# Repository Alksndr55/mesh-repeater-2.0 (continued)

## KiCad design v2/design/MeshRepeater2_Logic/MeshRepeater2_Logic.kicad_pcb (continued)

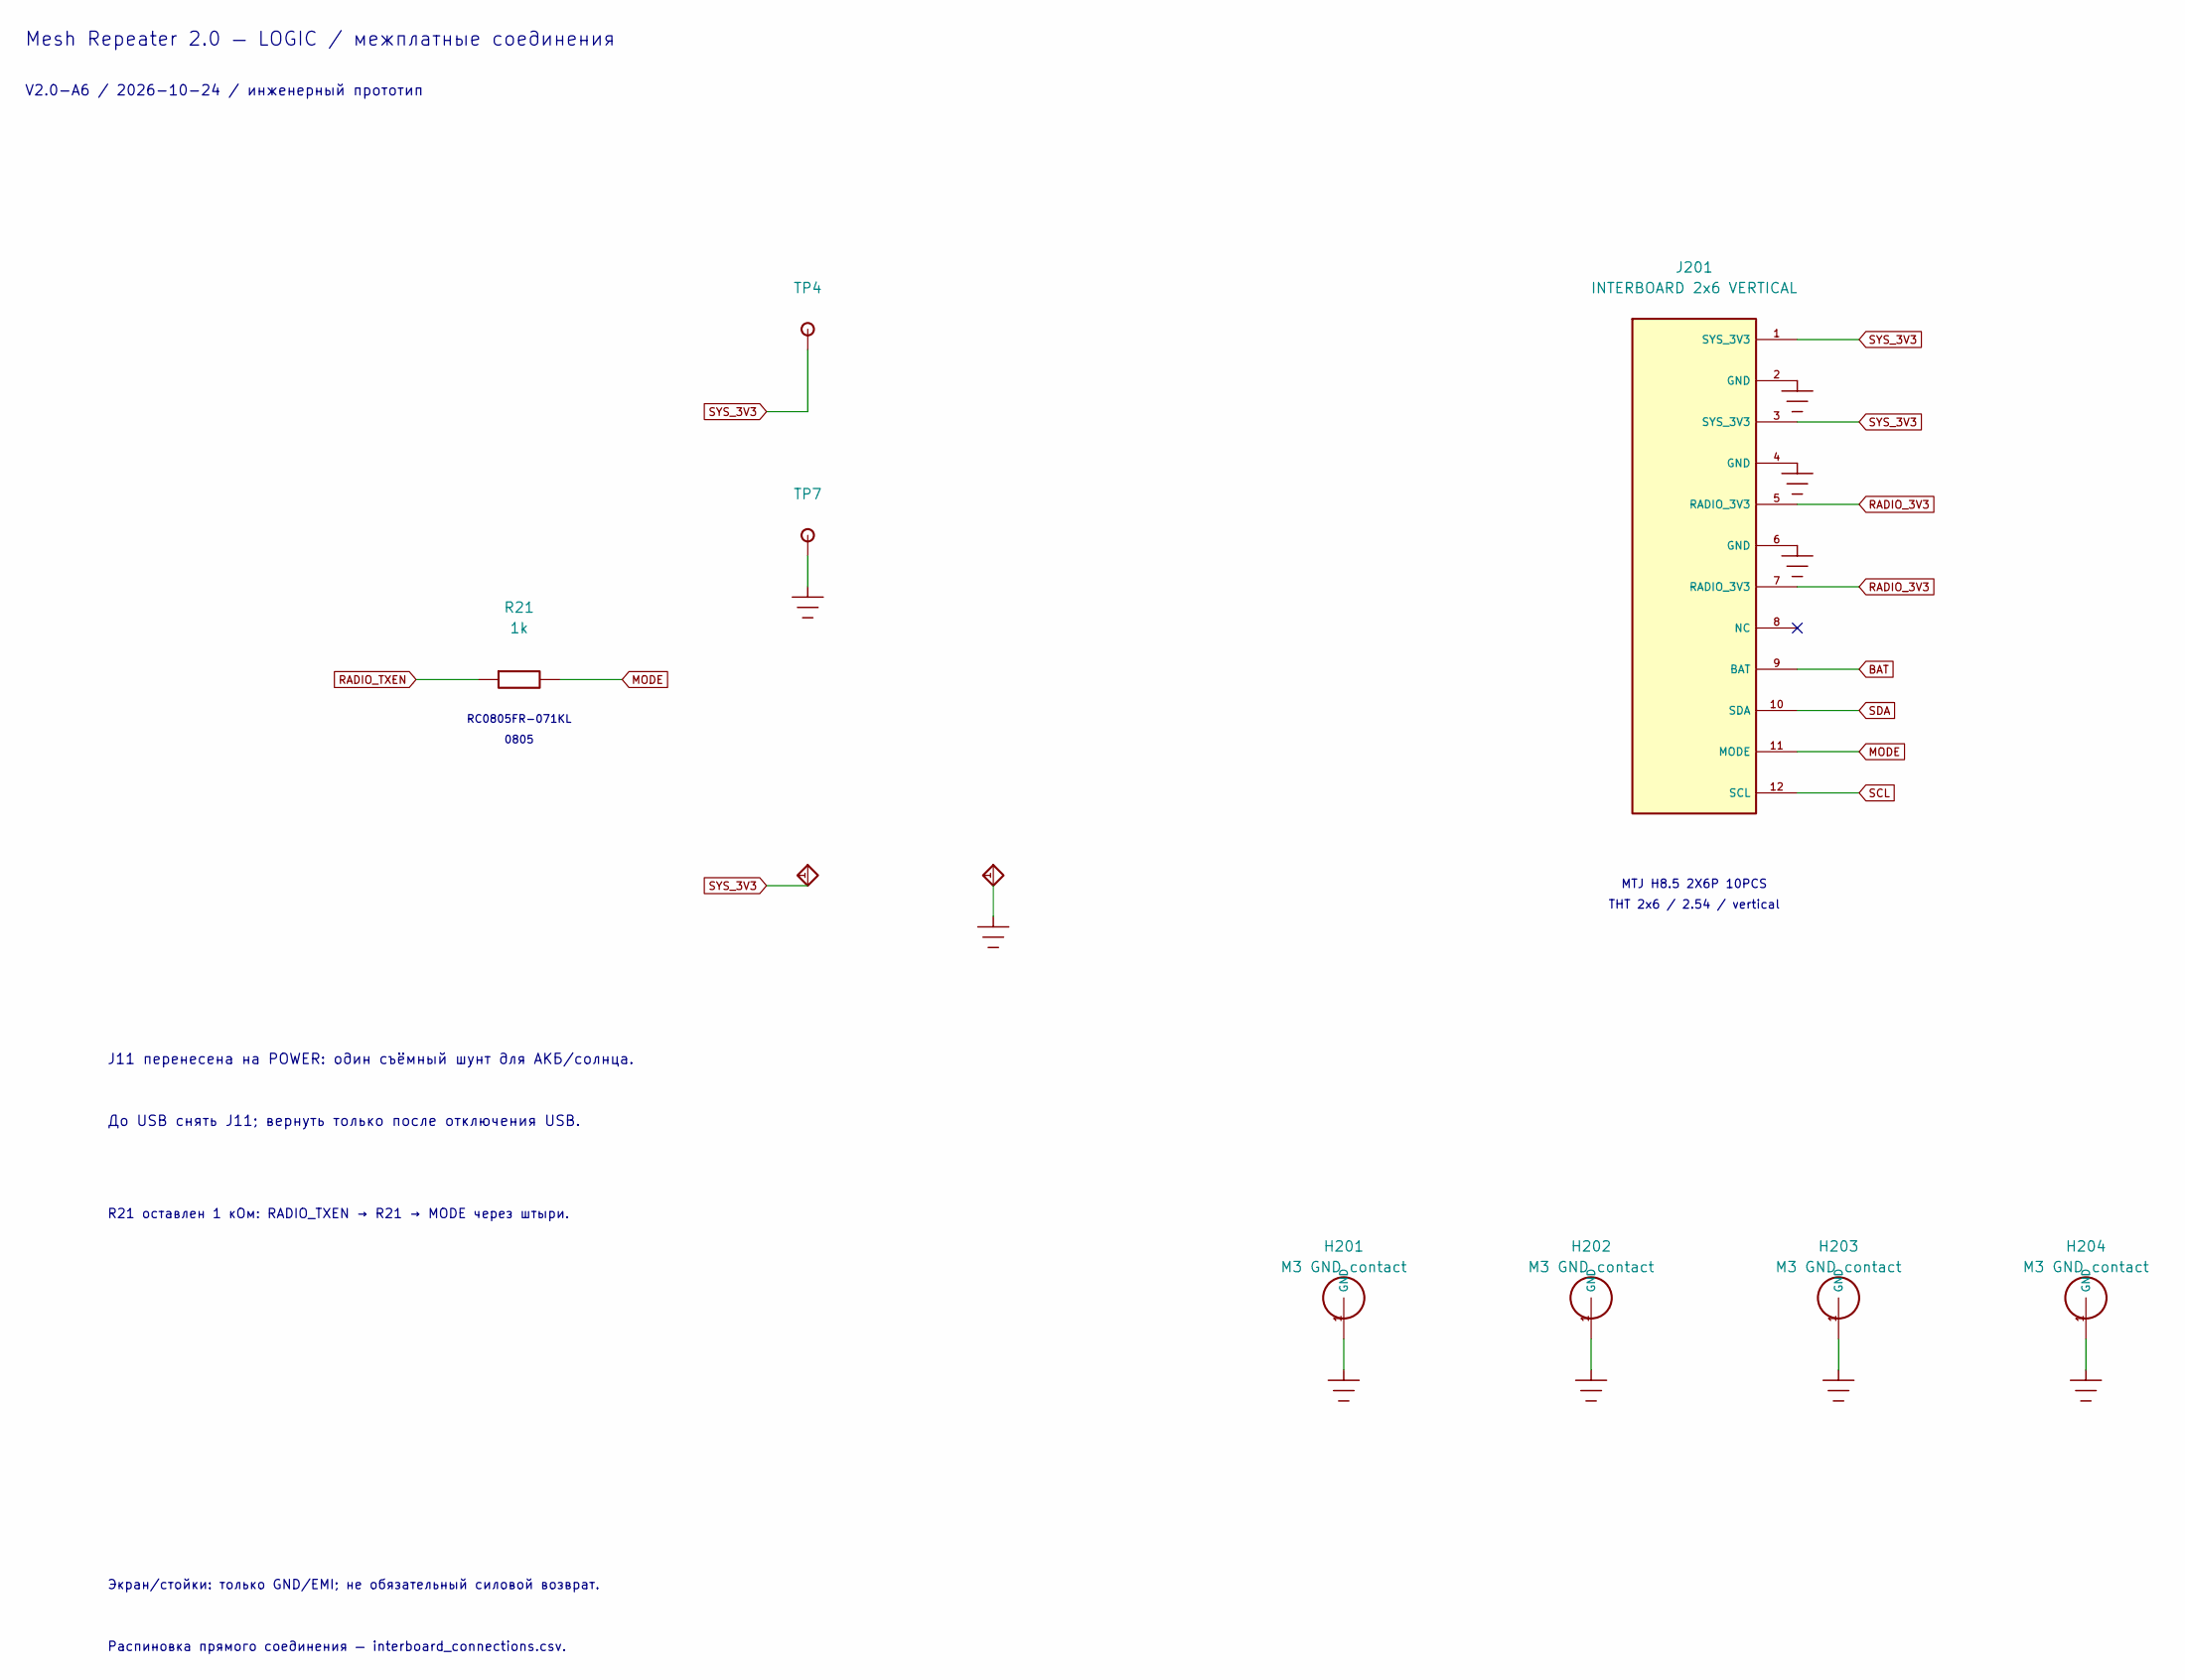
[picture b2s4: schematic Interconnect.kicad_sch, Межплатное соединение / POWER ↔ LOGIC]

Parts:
H201: M3 GND contact; GND_M3_D3.2_OD6__V2_H201; MPN PCB land M3 GND OD6 drill3.2
H202: M3 GND contact; GND_M3_D3.2_OD6__V2_H202; MPN PCB land M3 GND OD6 drill3.2
H203: M3 GND contact; GND_M3_D3.2_OD6__V2_H203; MPN PCB land M3 GND OD6 drill3.2
H204: M3 GND contact; GND_M3_D3.2_OD6__V2_H204; MPN PCB land M3 GND OD6 drill3.2
J201: INTERBOARD 2x6 VERTICAL; Ali_PinSocket_2x06_P2.54_H8.5_v2_mirror__V2_J201; MPN MTJ H8.5 2X6P 10PCS
R21: 1k; R_0805_2012Metric__V2_R21; MPN RC0805FR-071KL
TP4: SYS_3V3; TestPoint_Pad_D1.5mm__V2_TP4
TP7: GND; TestPoint_Pad_D1.5mm__V2_TP7

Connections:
BAT: J201.9 (BAT); also elsewhere on the board
GND: H201.1, H202.1, H203.1, H204.1, J201.2 (GND), J201.4 (GND), J201.6 (GND), TP7.1; also elsewhere on the board
MODE: J201.11 (MODE), R21.2
RADIO_3V3: J201.5 (RADIO_3V3), J201.7 (RADIO_3V3); also elsewhere on the board
RADIO_TXEN: R21.1; also elsewhere on the board
SCL: J201.12 (SCL); also elsewhere on the board
SDA: J201.10 (SDA); also elsewhere on the board
SYS_3V3: J201.1 (SYS_3V3), J201.3 (SYS_3V3), TP4.1; also elsewhere on the board

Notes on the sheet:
0805
THT 2x6 / 2.54 / vertical
V2.0-A6 / 2026-10-24 / инженерный прототип
R21 оставлен 1 кОм: RADIO_TXEN → R21 → MODE через штыри.
Экран/стойки: только GND/EMI; не обязательный силовой возврат.
J11 перенесена на POWER: один съёмный шунт для АКБ/солнца.
Mesh Repeater 2.0 — LOGIC / межплатные соединения
До USB снять J11; вернуть только после отключения USB.
RC0805FR-071KL
Распиновка прямого соединения — interboard_connections.csv.
MTJ H8.5 2X6P 10PCS

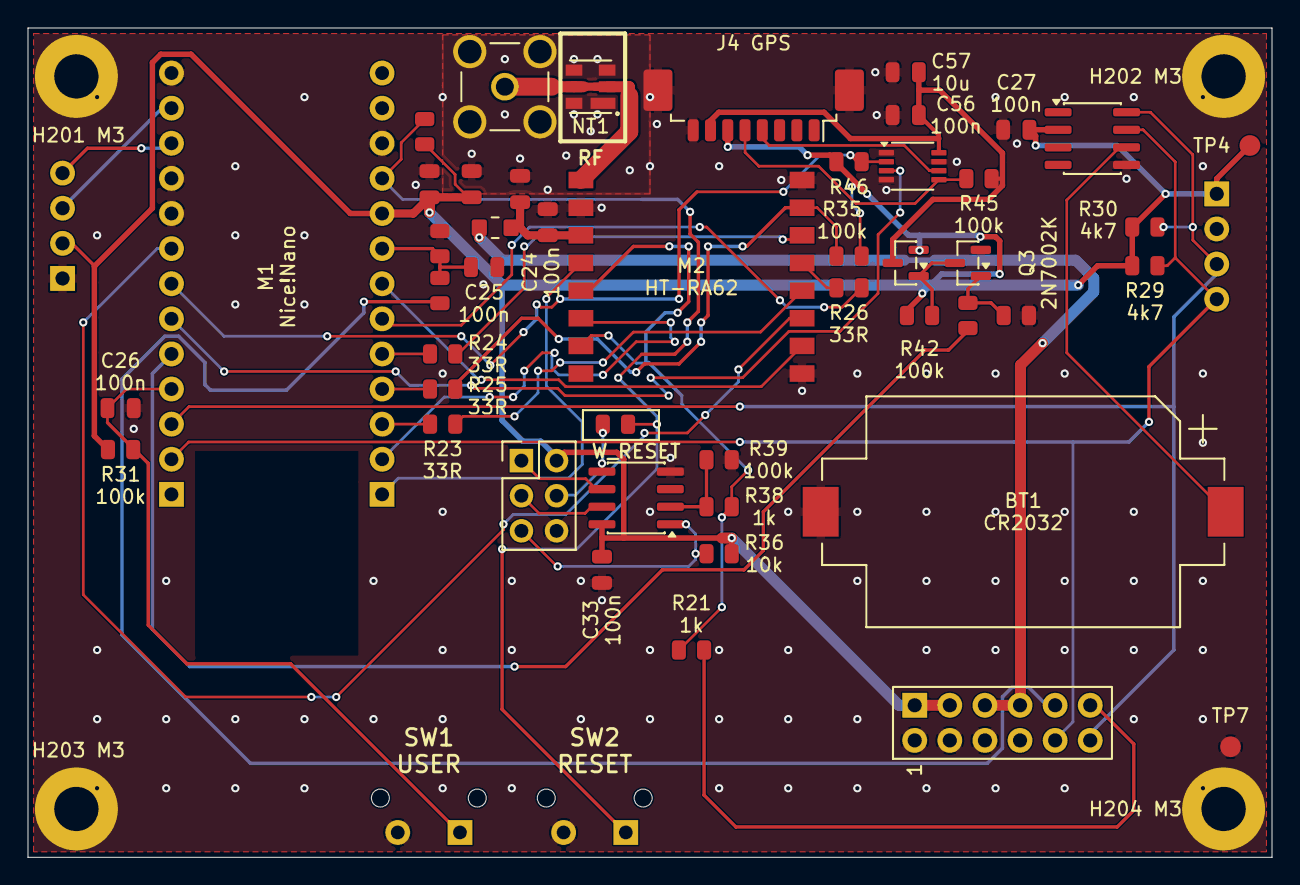
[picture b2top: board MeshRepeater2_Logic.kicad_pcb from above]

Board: 2 copper layers, 90.0 x 60.0 mm, 56 parts (0 on the bottom side), 42 nets.

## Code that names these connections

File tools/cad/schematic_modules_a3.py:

"""Compact module interconnect, controls and battery measurement."""
from schematic_core import Sheet

def build():
    s=Sheet('Modules','Nice!Nano, HT-RA62, управление и измерение батареи',3)
    s.sym('M1',88.9,80.01).sym('M2',215.9,80.01)
    for a,b in [(1,4),(2,6),(7,10),(21,11)]:s.wire(('M1',a),('M2',b))
    for ref,a,b,x in [('R23',3,12,153.67),('R24',5,14,153.67),('R25',4,15,153.67),('R26',6,13,175.26)]:
        y=s.pin('M1',a)[1]
        s.sym(ref,x,y,'R_H_REV' if ref=='R26' else 'R_H',label=(x-3.81,y-1.905,x+5.08,y-1.905))
        if ref=='R26':s.wire(('M1',a),(ref,2));s.wire((ref,1),('M2',b))
        else:s.wire(('M1',a),(ref,1));s.wire((ref,2),('M2',b))
    for a,n in [(1,'RADIO_RST'),(2,'RADIO_DIO1'),(7,'RADIO_BUSY'),(21,'RADIO_RXEN')]:s.label(n,(142.24,s.pin('M1',a)[1]))
    for pin in [12,13]:s.nc('M1',pin)
    from schematic_core import MODEL
    for pin in ([8] if MODEL.get('rf_connector') else [1,8]):s.nc('M2',pin)
    if MODEL.get('rf_connector'):
        rf_y=116.84 if MODEL.get('rf_filter_option') else 101.6
        s.sym('J13',317.5,rf_y,'COAX')
        ant=s.pin('M2',1)
        if MODEL.get('rf_filter_option'):
            s.sym('FL1',279.4,rf_y,'SAW')
            s.sym('NT1',279.4,104.14,'NETTIE')
            s.wire(ant,(246.38,ant[1]),(246.38,rf_y),('FL1',2))
            s.wire(('FL1',5),('J13',1))
            s.wire(('NT1',1),(259.08,104.14),(259.08,rf_y));s.dot((259.08,rf_y))
            s.wire(('NT1',2),(299.72,104.14),(299.72,rf_y));s.dot((299.72,rf_y))
            s.wire((254.0,rf_y),(254.0,119.38),(248.92,119.38));s.dot((254.0,rf_y))
            s.label('ANT_RF',(248.92,119.38),angle=180)
            s.wire((304.8,rf_y),(304.8,121.92),(299.72,121.92));s.dot((304.8,rf_y))
            s.label('ANT_SMA',(299.72,121.92),angle=180)
            for pin in (1,3,4,6):s.wire(('FL1',pin),(s.pin('FL1',pin)[0],132.08))
            s.wire((271.78,132.08),(287.02,132.08))
            s.dot((276.86,132.08));s.dot((281.94,132.08));s.ground((287.02,132.08),2.54)
            s.text('FL1 — опция 868–870 МГц, TX ≤ +13 dBm.\nДо установки разрезать медь NT1 под FL1.\nБез FL1 оставить NT1 целой.',266.7,151.13,1.05,'left')
        else:
            s.wire(ant,(246.38,ant[1]),(246.38,rf_y),('J13',1))
            s.label('ANT_RF',(269.24,rf_y))
        s.ground(('J13',2),2.54)
    for pin in [8,10,17,18,19,20,24,25,15,16]:s.net('M1',pin,5.08)
    s.nc('M1',14)
    # TXEN is DIO2: only a high-impedance sense is taken.
    tx=s.pin('M2',5);dio=s.pin('M2',7);x=182.88
    s.wire(tx,(x,tx[1]),(x,dio[1]),dio)
    s.wire((x,dio[1]),(x,114.3));s.dot((x,dio[1]))
    s.global_stub('RADIO_TXEN',(x,114.3),(187.96,114.3),angle=180)
    s.sym('R35',162.56,121.92,'R_H');s.net('R35',1,5.08)
    cs_y=s.pin('M2',15)[1]
    s.wire(('R35',2),(177.8,121.92),(177.8,cs_y));s.dot((177.8,cs_y))
    for ref,pins in [('M1',[11,22,23,26]),('M2',[2,9,16])]:
        coords=[s.pin(ref,n) for n in pins];y=max(p[1] for p in coords)+3.81
        for x,a in coords:s.wire((x,a),(x,y))
        s.wire((coords[0][0],y),(coords[-1][0],y))
        for x,a in coords[1:-1]:s.dot((x,y))
        s.ground((coords[1][0],y),2.54)
    # User-requested direct feed to the module3V3 pin.
    y=s.pin('M1',9)[1]
    s.wire(('M1',9),(30.48,y),(30.48,39.37))
    s.global_stub('SYS_3V3',(30.48,39.37),(25.4,39.37))
    s.sym('C23',251.46,73.66,'C_V').sym('C24',274.32,73.66,'C_V')
    y=s.pin('M2',3)[1]
    s.wire(('M2',3),(284.48,y));s.label('RADIO_LOCAL_3V3',(274.32,y))
    s.sym('FB1',251.46,38.1,'L_H')
    s.global_stub('RADIO_3V3',('FB1',1),(238.76,38.1))
    s.wire(('FB1',2),(284.48,38.1),(284.48,y))
    for ref in ['C23','C24']:
        x,_=s.pin(ref,1);s.wire((x,y),(ref,1));s.dot((x,y));s.ground((ref,2),2.54)
    s.sym('C21',218.44,167.64,'C_V').sym('C22',243.84,167.64,'C_V')
    s.wire((218.44,157.48),(243.84,157.48));s.global_stub('SYS_3V3',(218.44,157.48),(210.82,157.48))
    for ref in ['C21','C22']:
        x,_=s.pin(ref,1);s.wire((x,157.48),(ref,1));s.ground((ref,2),2.54)
    s.sym('R27',30.48,119.38,'R_V').sym('R28',30.48,139.7,'R_V').sym('C25',55.88,139.7,'C_V')
    s.net('R27',1,5.08)
    s.wire(('R27',2),(30.48,129.54),('R28',1));s.dot((30.48,129.54))
    s.wire((30.48,129.54),(55.88,129.54),('C25',1));s.global_stub('BAT_ADC',(55.88,129.54),(63.5,129.54),angle=180)
    s.ground(('R28',2),2.54);s.ground(('C25',2),2.54)
    s.sym('SW2',38.1,177.8,'SW_H').sym('SW1',91.44,177.8,'SW_H')
    for ref in ['SW2','SW1']:s.net(ref,1,5.08);s.ground((ref,2),2.54)
    s.sym('R31',104.14,149.86,'R_V').sym('C26',130.81,172.72,'C_V')
    s.net('R31',1,5.08)
    s.wire(('R31',2),(104.14,160.02),(130.81,160.02),('C26',1))
    s.global_stub('USER_BTN',(130.81,160.02),(140.97,160.02),angle=180);s.ground(('C26',2),2.54)
    adc_note=('ADC: BAT/2; τ ≈ 110 мс. Калибровка ADC.'
              if MODEL.get('battery_dividers') else 'ADC: BAT/2; установление ≈ 50 мс.')
    s.text(adc_note,15.24,157.48,1.27)
    s.text('SPI: 33 Ом у драйверов.\n'+('ANT: J13 / SMA, 50 Ом.\n' if MODEL.get('rf_connector') else 'ANT: штатный IPEX.\n')+'TXEN → MODE и watchdog.\nP1.06 свободен.\nBUSY=P0.29; GPS_EN=P0.24.\nGPS_EN=HIGH: питание GPS включено.',228.6,124.46,1.05)
    if MODEL.get('rf_connector'):
        s.text(MODEL['rf_connector']['module_configuration_ru'],317.5,152.4 if MODEL.get('rf_filter_option') else 137.16,1.05,'left')
    s.text('3V3 через J11 на POWER; RAW/BAT: NC. USB-зарядник отключить.\nСнять шунт J11 ДО подключения USB.\nВернуть J11 только после отключения USB.',142.24,188,1.27)
    s.text('POWER: J11 → NT2-звезда → две ветви. Модем: RADIO_3V3 → FB1 → RADIO_LOCAL_3V3.',142.24,210.82,1.15)
    s.text('FB1: DCR ≤20 мОм; около 3 мВ при 150 мА. Проверить броски питания при TX осциллографом.',142.24,218.44,1.15)
    return s

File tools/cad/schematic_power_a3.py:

"""Compact, explicitly wired power sheet for the editable S3 schematic.

Symbols retain their normal size. Coordinates use the 1.27 mm pin grid;
all visible reference/value properties retain the same upright two-line order.
"""
from schematic_core import Sheet,MODEL,PARTS


def _g(x, y):
    return round(x * 1.27, 5), round(y * 1.27, 5)


def _side_label(x, y):
    xx, yy = _g(x, y)
    return xx + 3.81, yy - 1.27, xx + 3.81, yy + 1.27


def _sym(sheet, ref, x, y, style=None, label=None):
    sheet.sym(ref, *_g(x, y), style=style, label=label)


def _ground(sheet, point):
    sheet.ground(point, length=2.54)


def _converter():
    s = Sheet('Converter', 'TPS63802 — питание и двухкаскадный LC-фильтр', 2)
    _sym(s, 'U2', 69, 66,
         label=(*_g(69, 44), *_g(69, 46)))
    _sym(s, 'L2', 69, 31, 'L_H')
    _sym(s, 'C12', 22, 60, 'C_V', _side_label(22, 60))
    _sym(s, 'C13', 39, 60, 'C_V', _side_label(39, 60))
    _sym(s, 'R15', 16, 76, 'R_V', _side_label(16, 76))
    _sym(s, 'R16', 16, 90, 'R_V', _side_label(16, 90))
    _sym(s, 'R17', 31, 90, 'R_V', _side_label(31, 90))
    _sym(s, 'C14', 94, 64, 'C_V', _side_label(94, 64))
    _sym(s, 'R13', 107, 64, 'R_V', _side_label(107, 64))
    _sym(s, 'R14', 107, 82, 'R_V', _side_label(107, 82))
    if 'R18' in PARTS:_sym(s, 'R18', 129, 82, 'R_V', _side_label(129, 82))
    _sym(s, 'TP3', 118, 52)
    if 'TP5' in PARTS:_sym(s, 'TP5', 140, 90)
    if 'TP7' in PARTS:_sym(s, 'TP7', 80, 87)

    # S4.5 reserve sites are wired directly to the same local input/output
    # rails as C12/C14. DNP denotes an empty site, not a chosen capacitance.
    for ref,x in [('C52',22),('C53',39),('C54',94),('C55',112)]:
        _sym(s,ref,x,34,'C_V',_side_label(x,34))
        _ground(s,(ref,2))
    s.wire(_g(16,52),_g(16,26),_g(39,26))
    for ref,x in [('C52',22),('C53',39)]:
        s.wire((ref,1),_g(x,26));s.dot(_g(x,26))
    s.wire(_g(94,26),_g(120,26),_g(120,56));s.dot(_g(120,56))
    for ref,x in [('C54',94),('C55',112)]:
        s.wire((ref,1),_g(x,26));s.dot(_g(x,26))

    # Both local input capacitors are normal vertical shunts below BAT.
    s.wire(_g(16, 52), _g(50, 52), _g(50, 56), ('U2', 10))
    s.global_stub('BAT_SYS' if MODEL.get('battery_monitor') else 'BAT',_g(39,26),_g(47,26),angle=180)
    for ref, x in [('C12', 22), ('C13', 39)]:
        s.wire((ref, 1), _g(x, 52)); s.dot(_g(x, 52))
        _ground(s, (ref, 2))

    # EN divider: BAT -> R15 -> EN_UV -> R16 -> GND.
    if MODEL.get('battery_monitor'):
        s.net('R15',1,7.62)
    else:
        s.wire(('R15', 1), _g(16, 52)); s.dot(_g(16, 52))
    s.wire(('R15', 2), _g(16, 82), ('R16', 1))
    s.wire(('U2', 1), _g(47, 66), _g(47, 82), _g(16, 82))
    s.dot(_g(16, 82)); s.label('EN_UV', _g(33, 82))
    _ground(s, ('R16', 2))

    s.wire(('U2', 9), _g(63, 31), ('L2', 1))
    s.wire(('U2', 7), _g(75, 31), ('L2', 2))
    s.label('LX1', _g(63, 43)); s.label('LX2', _g(75, 43))

    # C14 hangs below VOUT immediately before the additional LC network.
    if 'R55' in PARTS:
        _sym(s,'R55',125,56,'R_H',(*_g(125,48),*_g(125,50)))
        s.wire(('U2',6),('R55',1))
    else:s.wire(('U2', 6), _g(130, 56))
    s.label('SYS_PRE', _g(88, 56))
    s.wire(('C14', 1), _g(94, 56)); s.dot(_g(94, 56))
    _ground(s, ('C14', 2))
    s.wire(('TP3', 1), _g(118, 56)); s.dot(_g(118, 56))

    s.wire(('R13', 1), _g(107, 56)); s.dot(_g(107, 56))
    s.wire(('R13', 2), _g(107, 74), ('R14', 1))
    s.wire(('U2', 4), _g(88, 66), _g(88, 74), _g(107, 74))
    s.dot(_g(107, 74)); s.label('FB_SYS', _g(101, 74))
    _ground(s, ('R14', 2))

    s.wire(('U2', 3), _g(65, 90))
    s.wire(('U2', 8), _g(73, 90)); s.dot(_g(73, 90))
    s.wire(_g(65, 90), _g(80 if 'TP7' in PARTS else 73, 90))
    if 'TP7' in PARTS:s.wire(('TP7', 1), _g(80, 90))
    s.dot(_g(69, 90)); _ground(s, _g(69, 90))

    if 'R18' in PARTS:
        s.wire(('R18', 1), _g(129, 56)); s.dot(_g(129, 56))
        s.wire(('U2', 5), _g(88, 76), _g(88, 93), _g(140, 93))
        s.wire(('R18', 2), _g(129, 93))
        s.wire(('TP5', 1), _g(140, 93))
        s.dot(_g(129, 93));s.label('PG_SYS', _g(100, 93))
    else:s.nc('U2',5)

    # Actual parallel MLCC banks, one22mOhm resistor before each entire bank.
    _sym(s,'L3',138,56,'L_H')
    _sym(s,'L4',220,56,'L_H')
    if 'TP4' in PARTS:_sym(s,'TP4',292,52)
    _sym(s,'TP6',121,113)
    _sym(s,'TP1',39,48)
    if MODEL.get('battery_monitor'):
        tx,ty=s.pin('TP1',1)
        s.global_stub('BAT',(tx,ty),(tx-7.62,ty))
    else:
        s.wire(('TP1',1),_g(39,52));s.dot(_g(39,52))
    if 'R55' in PARTS:
        s.wire(('R55',2),('L3',1))
        s.wire(_g(130,56),_g(130,42));s.dot(_g(130,56))
        s.wire(_g(130,42),_g(135,42))
        s.label('SYS_LC_IN',_g(135,42))
    else:s.wire(_g(130,56),('L3',1))
    s.wire(('L3',2),('L4',1))
    s.label('FILTER_MID',_g(158,56))
    if 'TP8' in PARTS:
        s.sym('TP8',228.6,63.5)
        s.wire(('TP8',1),(228.6,71.12));s.dot((228.6,71.12))
        s.text('FILTER_MID',228.6,60.96,1.05,'')
    s.global_stub('FILTER_OUT',('L4',2),_g(251,56),angle=180)
    s.text('FILTER_OUT → J11 → NT2-звезда на листе Interconnect (POWER).',309.88,83.82,1.05)
    _ground(s,('TP6',1))
    for stage,(rref,xbase) in enumerate([('R40',185.42),('R41',299.72)]):
        s.sym(rref,xbase,88.9,'R_V')
        s.wire((xbase,71.12),(rref,1));s.dot((xbase,71.12))
        refs=MODEL['filter_bank']['refs'][stage]
        previous=s.pin(rref,2)
        for offset in range(0,len(refs),5):
            row=refs[offset:offset+5]; y=116.84+33.02*(offset//5)
            top=y-10.16;bottom=y+10.16
            xs=[xbase+7.62+16.51*i for i in range(len(row))]
            s.wire(previous,(xbase,top),(xs[-1],top))
            if offset:s.dot(previous)
            previous=(xbase,top)
            for ref,x in zip(row,xs):
                s.sym(ref,x,y,'C_V')
                s.wire((x,top),(ref,1));s.dot((x,top))
                s.wire((ref,2),(x,bottom))
            if len(xs)>1:s.wire((xs[0],bottom),(xs[-1],bottom))
            for x in xs[1:-1]:s.dot((x,bottom))
            s.wire((xs[-1],bottom),(xs[-1]+7.62,bottom))
            s.ground((xs[-1]+7.62,bottom),2.54)
        s.text('Каскад '+str(stage+1)+': Cэфф ≥ 330 мкФ при 3,3 В',xbase,177.8,1.05)

    # TXEN directly controls MODE through R21. RF_QUIET and diode OR removed.
    if 'R21' in PARTS:
        _sym(s, 'R21', 38, 110, 'R_H')
        s.wire(_g(24,110),('R21',1)); s.label('RADIO_TXEN',_g(24,110),global_=True)
        s.wire(('R21',2),_g(48,110),_g(48,76),('U2',2))
    else:
        s.wire(_g(48,110),_g(48,76),('U2',2))
        s.global_stub('MODE',_g(48,110),_g(40,110))
    if 'R21' in PARTS:s.label('MODE',_g(48,104))
    s.wire(('R17',1),_g(31,84),_g(48,84));s.dot(_g(48,84))
    _ground(s,('R17',2))
    s.flag('FILTER_OUT',360.68,180.34,5)
    s.text('SYS_PRE: 3,300 В; FB до L3. C14 — локальная ёмкость TPS63802.',15.24,160.02,1.15)
    if 'R55' in PARTS:
        s.text('R55: 47 мОм последовательно перед L3; падение 47 мВ/А. FB и C14 до R55.',185.42,185.42,1.05)
    s.text('TXEN=0: PFM; TXEN=1: forced PWM.',15.24,167.64,1.15)
    if MODEL.get('en_assembly_variants'):
        s.text('EN / Na: R15=40,2 кОм; R16=49,9 кОм; выкл.≈1,806 В; вкл.≈1,986 В.',15.24,173.99,1.05)
        s.text('EN / LTO: R15=130 кОм; R16=49,9 кОм; выкл.≈3,605 В; вкл.≈3,966 В (тип.).',15.24,178.435,1.05)
    else:s.text('EN: выкл. ≈1,806 В; вкл. ≈1,986 В.',15.24,175.26,1.15)
    s.text('J11 соединяет выход LC с SYS_3V3 всех нагрузок. Снять ДО USB; вернуть после отключения USB.',15.24,182.88,1.15)
    s.text('L3, L4: CDRH127/LDNP-2R4NC, 2,4 мкГн каждый. R40/R41: 22 мОм только в ветвях C.',15.24,193.04,1.15)
    s.text(MODEL['filter_bank']['schematic_note'],15.24,200.66,1.15)
    s.text('Cэфф ≥330 мкФ — требование приёмки; типовые кривые не дают гарантии. Проверить банк и запуск.',15.24,208.28,1.15)
    s.text('Проверить минимумы/максимумы 3V3 при подключении USB, PFM/PWM и скачке нагрузки.',15.24,215.9,1.15)
    s.text('C12 + C52: два локальных 10 мкФ / 16 В / 0805. C53, C54, C55: резерв 1206 / DNP.',15.24,222.25,1.15)
    return s

def build():
    return [_converter()]

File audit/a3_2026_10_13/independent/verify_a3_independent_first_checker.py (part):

"""Read-only independent review of the saved A3 native files.

Does not import any author's A3 placement, connectivity, or labelling gate.
Requires the root agent's ALL_CAD_FROZEN handoff. Never saves a board.
"""
from pathlib import Path
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import pcbnew as k
configure_headless()
HELD = []
PINMAP = {'1':'SYS_3V3','2':'GND','3':'SYS_3V3','4':'GND',
          '5':'RADIO_3V3','6':'GND','7':'RADIO_3V3','8':None,
          '9':'BAT','10':'SDA','11':'MODE','12':'SCL'}
SHUNTS = {'R1':'0.28R', 'R40':'22mR', 'R41':'22mR',
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          fps['POWER']['NT2'].IsNetTie()
          and native_tie_groups==[['1,2']]
          and p['NT2']['nets']=={'1':'SYS_3V3','2':'RADIO_3V3'})
    radio_power={(ref,pin) for ref,a in p.items() for pin,net in a['nets'].items() if net=='RADIO_3V3'}
    radio_logic={(ref,pin) for ref,a in l.items() for pin,net in a['nets'].items() if net=='RADIO_3V3'}
    local={(ref,pin) for ref,a in l.items() for pin,net in a['nets'].items() if net=='RADIO_LOCAL_3V3'}
    check('Separate RADIO branch runs from NT2 to two connector pins only',
          radio_power=={('NT2','2'),('J101','5'),('J101','7')},sorted(radio_power))
    check('RADIO on LOGIC feeds only FB1 input',radio_logic=={('J201','5'),('J201','7'),('FB1','1')},sorted(radio_logic))
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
